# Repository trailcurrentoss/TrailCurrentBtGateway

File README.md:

# TrailCurrent Bluetooth Gateway

Bluetooth Low Energy (BLE) gateway module that receives commands via Bluetooth and translates them into CAN bus messages for vehicle and trailer control. Part of the [TrailCurrent](https://trailcurrent.com) open-source vehicle platform.

## Hardware Overview

- **Microcontroller:** ESP32
- **Function:** BLE-to-CAN bus gateway for remote control of trailer devices
- **Key Features:**
  - BLE with secure bonding (MITM protection)
  - 8 independent device control channels
  - CAN bus interface at 500 kbps
  - Real-time sensor data relay (temperature, solar, battery)
  - Hierarchical PCB schematic design with FreeCAD enclosure

## Hardware Requirements

### Components

- **Microcontroller:** ESP32 with BLE support
- **CAN Transceiver:** Vehicle CAN bus interface (TX: GPIO 15, RX: GPIO 13)
- **LED Indicators:** 8 status LEDs (GPIOs 32, 33, 26, 14, 23, 19, 17, 4)

### KiCAD Library Dependencies

This project uses the consolidated [TrailCurrentKiCADLibraries](https://github.com/trailcurrentoss/TrailCurrentKiCADLibraries).

**Setup:**

```bash
# Clone the library
git clone git@github.com:trailcurrentoss/TrailCurrentKiCADLibraries.git

# Set environment variables (add to ~/.bashrc or ~/.zshrc)
export TRAILCURRENT_SYMBOL_DIR="/path/to/TrailCurrentKiCADLibraries/symbols"
export TRAILCURRENT_FOOTPRINT_DIR="/path/to/TrailCurrentKiCADLibraries/footprints"
export TRAILCURRENT_3DMODEL_DIR="/path/to/TrailCurrentKiCADLibraries/3d_models"
```

See [KICAD_ENVIRONMENT_SETUP.md](https://github.com/trailcurrentoss/TrailCurrentKiCADLibraries/blob/main/KICAD_ENVIRONMENT_SETUP.md) in the library repository for detailed setup instructions.

## Opening the Project

1. **Set up environment variables** (see Library Dependencies above)
2. **Open KiCAD:**
   ```bash
   kicad EDA/trailer-bt-gateway.kicad_pro
   ```
3. **Verify libraries load** - All symbol and footprint libraries should resolve without errors
4. **View 3D models** - Open PCB and press `Alt+3` to view the 3D visualization

### Schematic Sheets

The design uses a hierarchical schematic with dedicated sheets:
- **Root** - Top-level connections
- **Power** - Power distribution and regulation
- **CAN** - CAN bus transceiver interface
- **MCU** - ESP32 microcontroller and support circuits
- **Connectivity** - BLE and connector interfaces

## Firmware

See `src/` directory for PlatformIO-based firmware.

**Setup:**
```bash
# Install PlatformIO (if not already installed)
pip install platformio

# Build firmware
pio run

# Upload to board
pio run -t upload
```

### BLE Service

The gateway exposes a BLE service for device control and sensor data:

- **Service UUID:** `e5553316-4ef1-4a9c-9941-a15f1d2394ea`
- **Device Control:** 8 independent channels with on/off/all control
- **Sensor Data Characteristics:**
  - MPPT solar controller data
  - Temperature and humidity readings
  - Battery shunt monitor data

### CAN Bus Protocol

**Transmit (Gateway to Bus):**
- ID `0x18`: Device control commands (8 bytes)

**Receive (Bus to Gateway):**

| CAN ID | Description |
|--------|-------------|
| 0x1B | Light/device status (8 bytes) |
| 0x1F | Temperature/humidity data |
| 0x23 | Battery shunt data (voltage, current, SOC) |
| 0x24 | Battery wattage data |
| 0x2C | MPPT solar panel data |
| 0x2D | MPPT solar current data |

## Manufacturing

- **PCB Files:** Ready for fabrication via standard PCB services (JLCPCB, OSH Park, etc.)
- **BOM Generation:** Export BOM from KiCAD schematic (Tools > Generate BOM)
- **Enclosure:** FreeCAD design included in `CAD/` directory
- **JLCPCB Assembly:** See [BOM_ASSEMBLY_WORKFLOW.md](https://github.com/trailcurrentoss/TrailCurrentKiCADLibraries/blob/main/BOM_ASSEMBLY_WORKFLOW.md) for detailed assembly workflow

## Project Structure

```
├── CAD/                          # FreeCAD enclosure design
├── EDA/                          # KiCAD hardware design files
│   ├── trailer-bt-gateway.kicad_pro
│   ├── trailer-bt-gateway.kicad_sch  # Root schematic
│   ├── can.kicad_sch             # CAN subsystem
│   ├── connectivity.kicad_sch    # Connectivity subsystem
│   ├── mcu.kicad_sch             # MCU subsystem
│   ├── power.kicad_sch           # Power subsystem
│   └── trailer-bt-gateway.kicad_pcb  # PCB layout
├── src/                          # Firmware source
│   ├── main.cpp                  # Main BLE/CAN application
│   ├── globals.h                 # Pin definitions and debug macros
│   └── canHelper.h               # CAN bus configuration
└── platformio.ini                # Build configuration
```

## License

MIT License - See LICENSE file for details.

This is open source hardware. You are free to use, modify, and distribute these designs under the terms of the MIT license.

## Contributing

Improvements and contributions are welcome! Please submit issues or pull requests.

## Support

For questions about:
- **KiCAD setup:** See [KICAD_ENVIRONMENT_SETUP.md](https://github.com/trailcurrentoss/TrailCurrentKiCADLibraries/blob/main/KICAD_ENVIRONMENT_SETUP.md)
- **Assembly workflow:** See [BOM_ASSEMBLY_WORKFLOW.md](https://github.com/trailcurrentoss/TrailCurrentKiCADLibraries/blob/main/BOM_ASSEMBLY_WORKFLOW.md)

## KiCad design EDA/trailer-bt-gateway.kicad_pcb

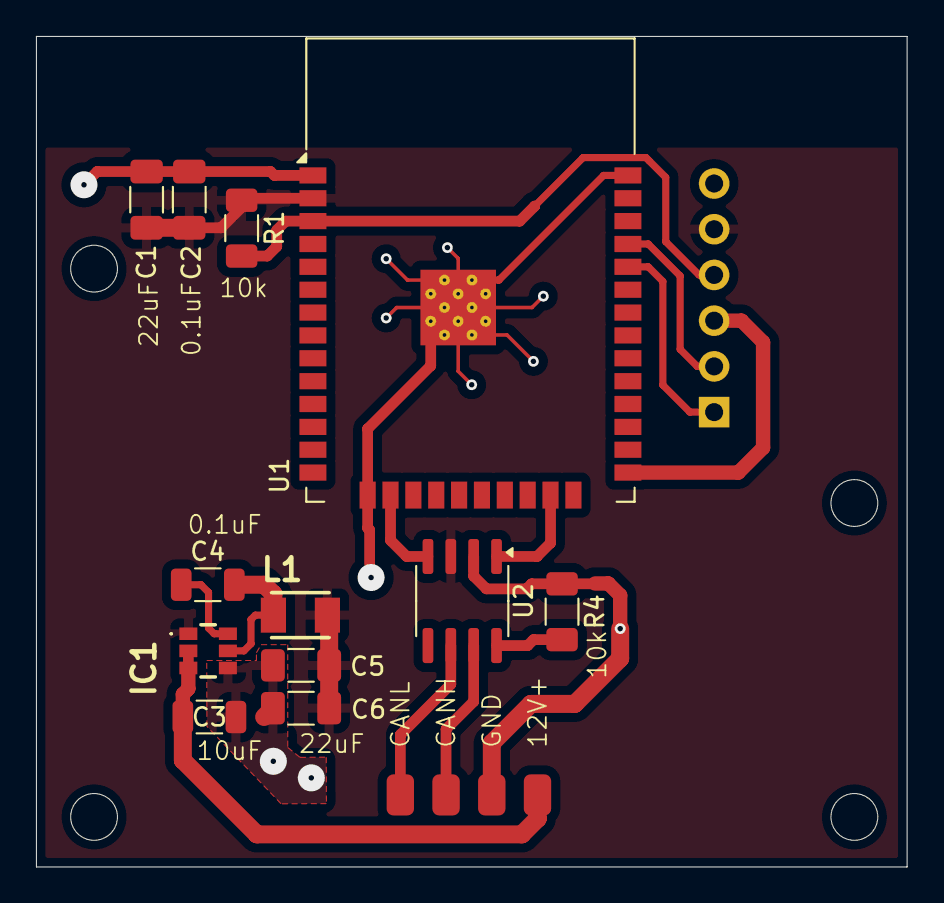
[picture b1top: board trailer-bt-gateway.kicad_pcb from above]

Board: 2 copper layers, 48.4 x 46.1 mm, 14 parts (1 on the bottom side), 14 nets.

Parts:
C1, C5, C6: 22uF; C_1206_3216Metric_Pad1.33x1.80mm_HandSolder
C2: 0.1uF; C_1206_3216Metric_Pad1.33x1.80mm_HandSolder
C3: 10uF; C_1206_3216Metric
C4: 100nF; C_1206_3216Metric
IC1: AP63203WU-7; AP63203WU7
J1: Conn_01x06; PinHeader_1x06_P2.54mm_Horizontal
J2: Conn_01x04; CAN_PLUS_POWER
L1: NLV32T-3R9J-EF (3.9uH); NLV32T-3R9J-EF
R1, R4: 10k; R_1206_3216Metric_Pad1.30x1.75mm_HandSolder
U1: ESP32-WROOM-32
U2: SN65HVD230; SOIC-8_3.9x4.9mm_P1.27mm

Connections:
+3.3V: C1.1, C2.1, C5.1, C6.1, IC1.1 (FB), J1.5, L1.2, R1.1, U1.2 (VDD), U2.3 (VCC)
+12V: C3.1, IC1.2 (EN), IC1.3 (VIN), J2.1
CANH: J2.3, U2.7 (CANH)
CANL: J2.4, U2.6 (CANL)
CAN_RX: U1.16 (IO13), U2.4 (R)
CAN_TX: U1.23 (IO15), U2.1 (D)
EN: J1.4, R1.2, U1.3 (EN)
ESP32_RX: J1.1, U1.34 (RXD0/IO3)
ESP32_TX: J1.2, U1.35 (TXD0/IO1)
GND: C1.2, C2.2, C3.2, C5.2, C6.2, IC1.4 (GND), J1.6, J2.2, R4.1, U1.1 (GND), U1.15 (GND), U1.38 (GND), U1.39 (GND), U2.2 (GND)
IO0: J1.3, U1.25 (IO0)
unnamed: C4.1, IC1.6 (BST)
unnamed: C4.2, IC1.5 (SW), L1.1
unnamed: R4.2, U2.8 (Rs)

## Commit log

2026-02-12 Starting project
2026-02-14 Fixining license file and CAD used to generate website images
2026-02-14 Update docs: replace Codeberg URLs with GitHub references
2026-02-23 Add trailcurrent.com link to README
